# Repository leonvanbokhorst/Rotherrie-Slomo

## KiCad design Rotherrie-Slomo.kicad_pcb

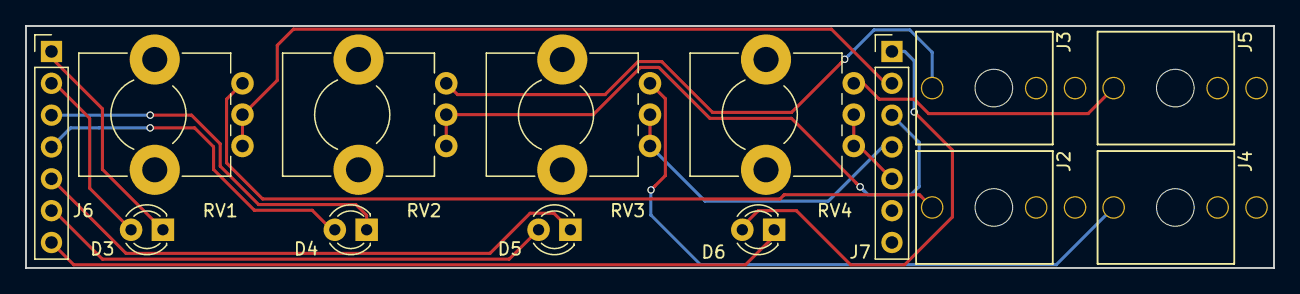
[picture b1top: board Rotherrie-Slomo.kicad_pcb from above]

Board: 2 copper layers, 99.6 x 19.3 mm, 14 parts (0 on the bottom side), 17 nets.

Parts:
D3, D4, D5, D6: LED_Dual_2pin; LED_D3.0mm
J2, J3, J4, J5: JACK_2P; PJ301M-12-hole
J6, J7: CONN_01X07; Pin_Header_Straight_1x07_Pitch2.54mm
RV1, RV2, RV3, RV4: 500k; Potentiometer_Bourns_PTV09A-1_Horizontal

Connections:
GND: J2.1, J3.1, J4.1, J5.1, J7.6, J7.7
LED1: D3.1, J6.1
LED1R: D3.2, J6.2
LED2: D4.1, J6.3
LED2R: D4.2, J6.4
LED3: D5.1, J6.5
LED3R: D5.2, J6.6
LED4: D6.1, J6.7
LED4R: D6.2, J7.1
POT1: J7.2, RV1.2, RV1.3
POT2: J7.3, RV2.2, RV2.3
POT3: J7.4, RV3.2, RV3.3
POT4: J7.5, RV4.2, RV4.3
WAVE1: J2.3, RV1.1
WAVE2: J3.3, RV2.1
WAVE3: J4.3, RV3.1
WAVE4: J5.3, RV4.1

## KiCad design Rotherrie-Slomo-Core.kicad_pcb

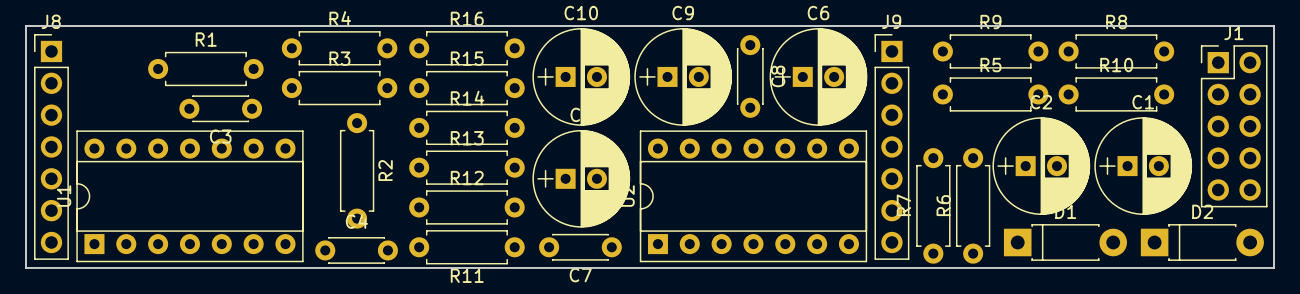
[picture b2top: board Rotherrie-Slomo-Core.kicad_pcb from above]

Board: 2 copper layers, 99.6 x 19.3 mm, 33 parts (0 on the bottom side), 27 nets.

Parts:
C1, C2: 22uF; CP_Radial_D7.5mm_P2.50mm
C3, C4, C7, C8: 100nF; C_Disc_D4.3mm_W1.9mm_P5.00mm
C5, C6, C9, C10: 100uF; CP_Radial_D7.5mm_P2.50mm
D1, D2: 1N5817; D_DO-41_SOD81_P7.62mm_Horizontal
J1: CONN_02X05; Pin_Header_Straight_2x05_Pitch2.54mm
J8, J9: CONN_01X07; Pin_Header_Straight_1x07_Pitch2.54mm
R1, R2, R3, R4: 1k; R_Axial_DIN0207_L6.3mm_D2.5mm_P7.62mm_Horizontal
R5, R6, R9, R10, R11, R13, R14, R16: 4.7k; R_Axial_DIN0207_L6.3mm_D2.5mm_P7.62mm_Horizontal
R7, R8, R12, R15: 100k; R_Axial_DIN0207_L6.3mm_D2.5mm_P7.62mm_Horizontal
U1, U2: TL074; DIP-14_W7.62mm_Socket

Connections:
GND: C1.2, C2.1, C3.1, C4.1, C5.2, C6.2, C7.1, C8.1, C9.2, C10.2, D1.2, D2.1, J1.3, J1.4, J1.5, J1.6, J1.7, J1.8, J8.7, J9.7, R1.2, R2.2, R3.2, R4.2, R5.2, R6.2, R11.2, R14.2
LED1: J8.2, U1.1
LED1R: J8.3, R1.1, U1.2
LED2: J8.5, U1.7
LED2R: J8.6, R2.1, U1.6
LED3: J9.2, U1.8
LED3R: J9.3, R3.1, U1.9
LED4: J9.5, U1.14
LED4R: J9.6, R4.1, U1.13
unnamed: C5.1, R7.1, U2.2
unnamed: C6.1, R8.1, U2.6
unnamed: C9.1, R12.1, U2.9
unnamed: C10.1, R15.1, U2.13
unnamed: R5.1, R9.2, U2.3
unnamed: R9.1, U2.1
unnamed: R10.1, U2.7
unnamed: R6.1, R10.2, U2.5
unnamed: R11.1, R13.2, U2.10
unnamed: R13.1, U2.8
unnamed: R14.1, R16.2, U2.12
unnamed: R16.1, U2.14
POT1: J8.1, R7.2
POT2: J8.4, R8.2
POT3: J9.1, R12.2
POT4: J9.4, R15.2
VCC: C1.1, C4.2, C7.2, D1.1, J1.9, J1.10, U1.4, U2.4
VEE: C2.2, C3.2, C8.2, D2.2, J1.1, J1.2, U1.11, U2.11

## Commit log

2017-09-07 Power scematic
2017-09-07 Bipolar LED schematic
2017-09-07 First WAVE unit schematic
2017-09-08 Oscillator section done
2017-09-08 Part associations made. 16pin connector reduced to 10 pin
2017-09-08 Added jack connectors to schematic
2017-09-08 Import Eurorack lib. Finished part associations. Generated net list.
2017-09-08 Rerouting from logic to controller board
2017-09-08 Core board first setup
2017-09-09 Core board component layout
2017-09-09 Trouble routing core board. Redesign of header pins needed
2017-09-09 Reroute controller board
2017-09-09 Controller board rerouted and added GND plane
2017-09-09 Finetuning controller board routing
